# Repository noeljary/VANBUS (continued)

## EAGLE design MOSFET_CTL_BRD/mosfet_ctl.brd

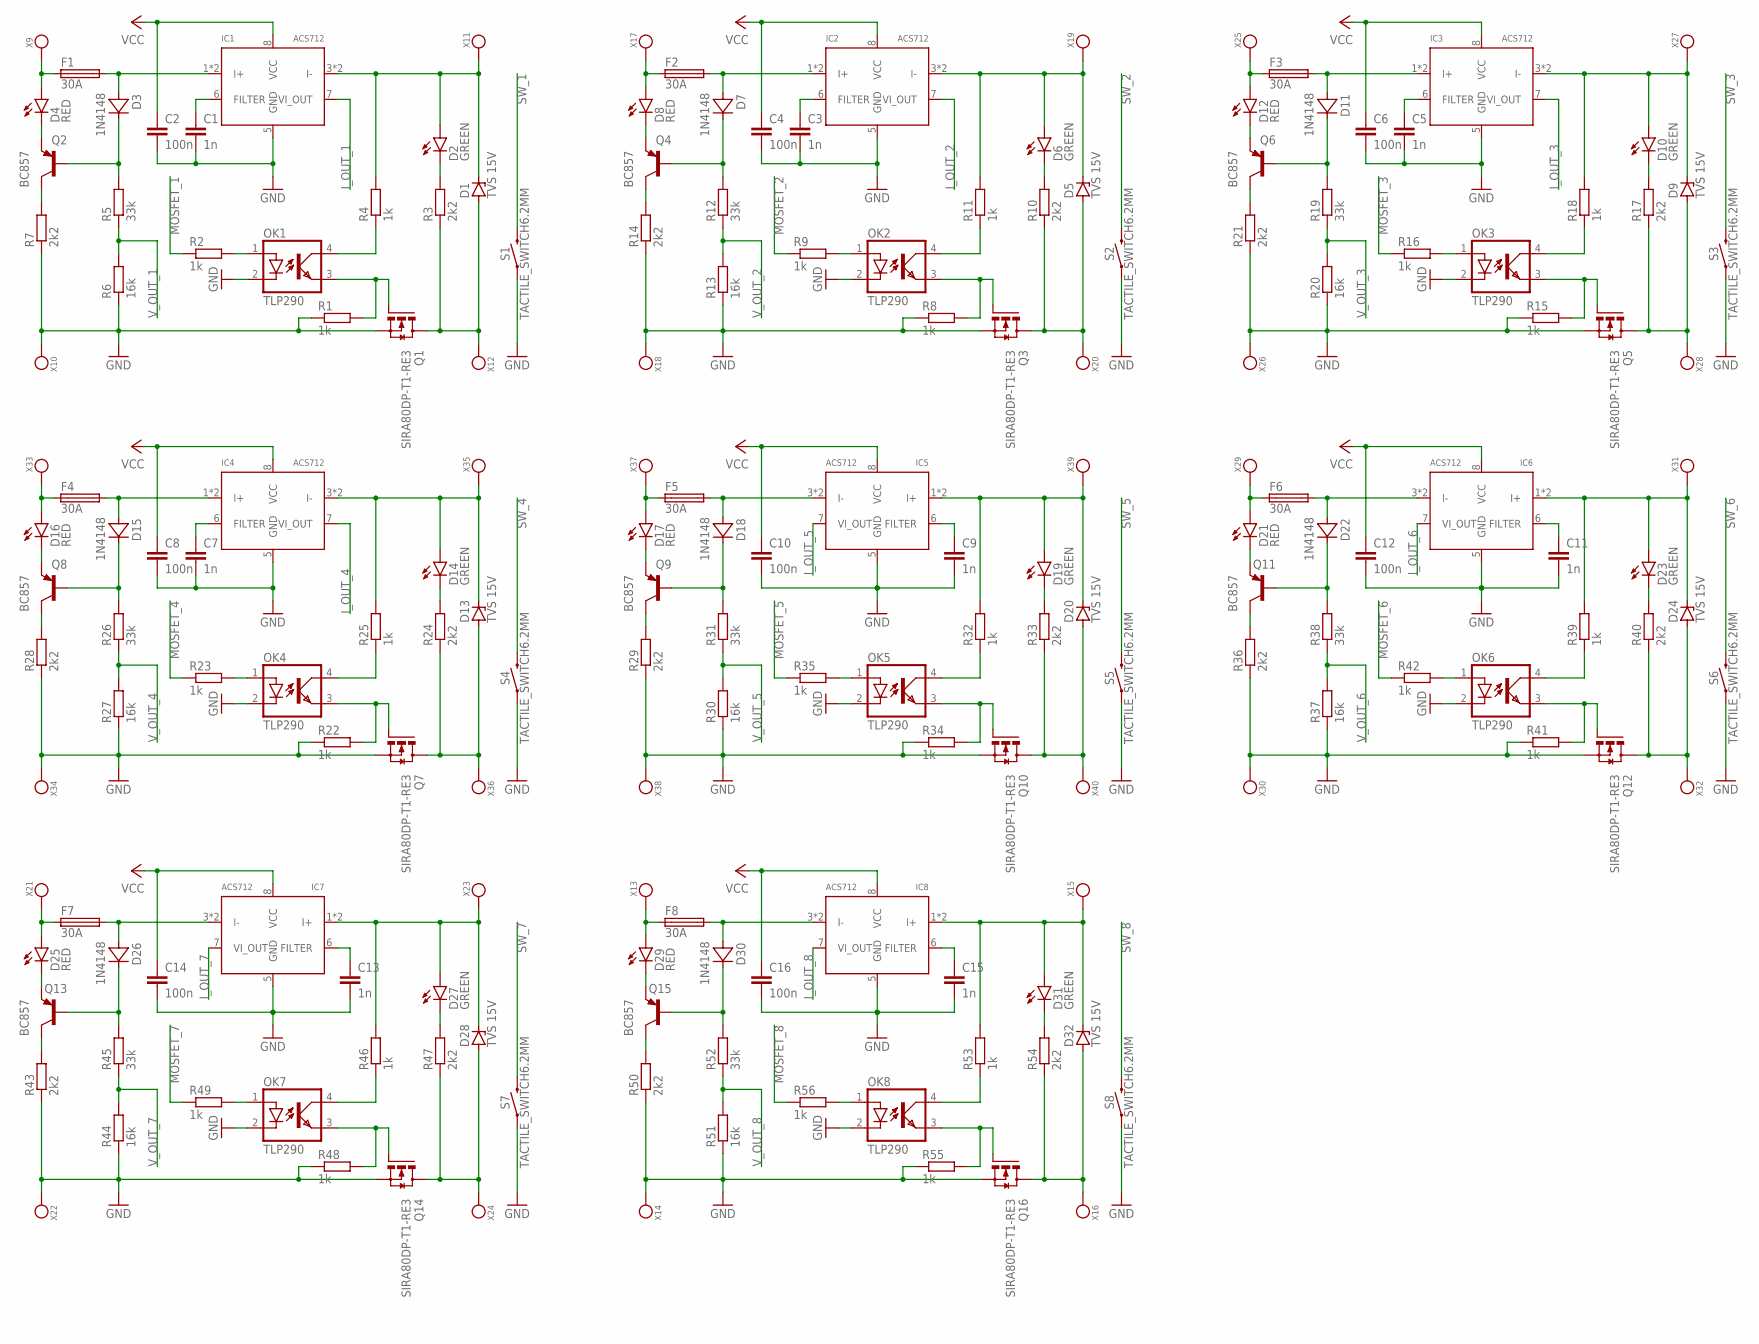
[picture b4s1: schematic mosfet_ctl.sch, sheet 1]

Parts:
C1, C3, C5, C7, C9, C11, C13, C15: 1n; C0805
C2, C4, C6, C8, C10, C12, C14, C16: 100n; C0805
D1, D5, D9, D13, D20, D24, D28, D32: TVS 15V; DO214AC
D2, D6, D10, D14, D19, D23, D27, D31: GREEN; CHIPLED_1206
D3, D7, D11, D15, D18, D22, D26, D30: 1N4148; SOD123
D4, D8, D12, D16, D17, D21, D25, D29: RED; CHIPLED_1206
F1, F2, F3, F4, F5, F6, F7, F8: 30A; KEYSTONE_3557-2
IC1, IC2, IC3, IC4, IC5, IC6, IC7, IC8: ACS712; SO08
OK1, OK2, OK3, OK4, OK5, OK6, OK7, OK8: TLP290; SO04
Q1, Q3, Q5, Q7, Q10, Q12, Q14, Q16: SIRA80DP-T1-RE3; POWERPAK-SO8
Q2, Q4, Q6, Q8, Q9, Q11, Q13, Q15: BC857; SOT23
R1, R2, R4, R8, R9, R11, R15, R16, R18, R22, R23, R25, R32, R34, R35, R39, R41, R42, R46, R48, R49, R53, R55, R56: 1k; R0805
R3, R7, R10, R14, R17, R21, R24, R28, R29, R33, R36, R40, R43, R47, R50, R54: 2k2; R0805
R5, R12, R19, R26, R31, R38, R45, R52: 33k; R0805
R6, R13, R20, R27, R30, R37, R44, R51: 16k; R0805
S1, S2, S3, S4, S5, S6, S7, S8: TACTILE_SWITCH6.2MM; TACTILE_SWITCH_SMD_6.2MM
X9, X10, X11, X12, X13, X14, X15, X16, X17, X18, X19, X20, X21, X22, X23, X24, X25, X26, X27, X28, X29, X30, X31, X32, X33, X34, X35, X36, X37, X38, X39, X40: KEYSTONE_7800

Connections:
GND: C1.2, C2.2, C3.2, C4.2, C5.2, C6.2, C7.2, C8.2, C9.2, C10.2, C11.2, C12.2, C13.2, C14.2, C15.2, C16.2, IC1.5 (GND), IC2.5 (GND), IC3.5 (GND), IC4.5 (GND), IC5.5 (GND), IC6.5 (GND), IC7.5 (GND), IC8.5 (GND), OK1.2 (C), OK2.2 (C), OK3.2 (C), OK4.2 (C), OK5.2 (C), OK6.2 (C), OK7.2 (C), OK8.2 (C), Q1.1 (S), Q1.2 (S), Q3.1 (S), Q3.2 (S), Q5.1 (S), Q5.2 (S), Q7.1 (S), Q7.2 (S), Q10.1 (S), Q10.2 (S), Q12.1 (S), Q12.2 (S), Q14.1 (S), Q14.2 (S), Q16.1 (S), Q16.2 (S), R1.1, R6.1, R7.1, R8.1, R13.1, R14.1, R15.1, R20.1, R21.1, R22.1, R27.1, R28.1, R29.1, R30.1, R34.1, R36.1, R37.1, R41.1, R43.1, R44.1, R48.1, R50.1, R51.1, R55.1, S1.A1 (1), S1.A2 (1), S2.A1 (1), S2.A2 (1), S3.A1 (1), S3.A2 (1), S4.A1 (1), S4.A2 (1), S5.A1 (1), S5.A2 (1), S6.A1 (1), S6.A2 (1), S7.A1 (1), S7.A2 (1), S8.A1 (1), S8.A2 (1), X10.1, X10.2, X10.3, X10.4, X10.5, X10.6, X14.1, X14.2, X14.3, X14.4, X14.5, X14.6, X18.1, X18.2, X18.3, X18.4, X18.5, X18.6, X22.1, X22.2, X22.3, X22.4, X22.5, X22.6, X26.1, X26.2, X26.3, X26.4, X26.5, X26.6, X30.1, X30.2, X30.3, X30.4, X30.5, X30.6, X34.1, X34.2, X34.3, X34.4, X34.5, X34.6, X38.1, X38.2, X38.3, X38.4, X38.5, X38.6; also elsewhere on the board
I_OUT_1: IC1.7 (VI_OUT); also elsewhere on the board
I_OUT_2: IC2.7 (VI_OUT); also elsewhere on the board
I_OUT_3: IC3.7 (VI_OUT); also elsewhere on the board
I_OUT_4: IC4.7 (VI_OUT); also elsewhere on the board
I_OUT_5: IC5.7 (VI_OUT); also elsewhere on the board
I_OUT_6: IC6.7 (VI_OUT); also elsewhere on the board
I_OUT_7: IC7.7 (VI_OUT); also elsewhere on the board
I_OUT_8: IC8.7 (VI_OUT); also elsewhere on the board
MOSFET_1: R2.1; also elsewhere on the board
MOSFET_2: R9.1; also elsewhere on the board
MOSFET_3: R16.1; also elsewhere on the board
MOSFET_4: R23.1; also elsewhere on the board
MOSFET_5: R35.1; also elsewhere on the board
MOSFET_6: R42.1; also elsewhere on the board
MOSFET_7: R49.1; also elsewhere on the board
MOSFET_8: R56.1; also elsewhere on the board
unnamed: D4.A, F1.1, F1.3 (1), X9.1, X9.2, X9.3, X9.4, X9.5, X9.6
unnamed: D3.A, F1.2, F1.4 (2), IC1.1 (I+), IC1.2 (I+)
unnamed: D4.C, Q2.2 (E)
unnamed: D3.C, Q2.3 (B), R5.2
unnamed: Q2.1 (C), R7.2
unnamed: C1.1, IC1.6 (FILTER)
unnamed: D2.C, R3.2
unnamed: OK1.1 (A), R2.2
unnamed: OK1.4 (COL), R4.1
unnamed: D1.C, D2.A, IC1.3 (I-), IC1.4 (I-), R4.2, X11.1, X11.2, X11.3, X11.4, X11.5, X11.6
unnamed: OK1.3 (EMIT), Q1.3 (G), Q1.4 (G), R1.2
unnamed: D1.A, Q1.5 (D), Q1.6 (D), Q1.7 (D), Q1.8 (D), Q1.9 (D), R3.1, X12.1, X12.2, X12.3, X12.4, X12.5, X12.6
unnamed: D29.A, F8.1, F8.3 (1), X13.1, X13.2, X13.3, X13.4, X13.5, X13.6
unnamed: D30.A, F8.2, F8.4 (2), IC8.3 (I-), IC8.4 (I-)
unnamed: D29.C, Q15.2 (E)
unnamed: D30.C, Q15.3 (B), R52.2
unnamed: Q15.1 (C), R50.2
unnamed: C15.1, IC8.6 (FILTER)
unnamed: D31.C, R54.2
unnamed: OK8.1 (A), R56.2
unnamed: OK8.4 (COL), R53.1
unnamed: D31.A, D32.C, IC8.1 (I+), IC8.2 (I+), R53.2, X15.1, X15.2, X15.3, X15.4, X15.5, X15.6
unnamed: OK8.3 (EMIT), Q16.3 (G), Q16.4 (G), R55.2
unnamed: D32.A, Q16.5 (D), Q16.6 (D), Q16.7 (D), Q16.8 (D), Q16.9 (D), R54.1, X16.1, X16.2, X16.3, X16.4, X16.5, X16.6
unnamed: D8.A, F2.1, F2.3 (1), X17.1, X17.2, X17.3, X17.4, X17.5, X17.6
unnamed: D7.A, F2.2, F2.4 (2), IC2.1 (I+), IC2.2 (I+)
unnamed: D8.C, Q4.2 (E)
unnamed: D7.C, Q4.3 (B), R12.2
unnamed: Q4.1 (C), R14.2
unnamed: C3.1, IC2.6 (FILTER)
unnamed: D6.C, R10.2
unnamed: OK2.1 (A), R9.2
unnamed: OK2.4 (COL), R11.1
unnamed: D5.C, D6.A, IC2.3 (I-), IC2.4 (I-), R11.2, X19.1, X19.2, X19.3, X19.4, X19.5, X19.6
unnamed: OK2.3 (EMIT), Q3.3 (G), Q3.4 (G), R8.2
unnamed: D5.A, Q3.5 (D), Q3.6 (D), Q3.7 (D), Q3.8 (D), Q3.9 (D), R10.1, X20.1, X20.2, X20.3, X20.4, X20.5, X20.6
unnamed: D25.A, F7.1, F7.3 (1), X21.1, X21.2, X21.3, X21.4, X21.5, X21.6
unnamed: D26.A, F7.2, F7.4 (2), IC7.3 (I-), IC7.4 (I-)
unnamed: D25.C, Q13.2 (E)
unnamed: D26.C, Q13.3 (B), R45.2
unnamed: Q13.1 (C), R43.2
unnamed: C13.1, IC7.6 (FILTER)
unnamed: D27.C, R47.2
unnamed: OK7.1 (A), R49.2
unnamed: OK7.4 (COL), R46.1
unnamed: D27.A, D28.C, IC7.1 (I+), IC7.2 (I+), R46.2, X23.1, X23.2, X23.3, X23.4, X23.5, X23.6
unnamed: OK7.3 (EMIT), Q14.3 (G), Q14.4 (G), R48.2
unnamed: D28.A, Q14.5 (D), Q14.6 (D), Q14.7 (D), Q14.8 (D), Q14.9 (D), R47.1, X24.1, X24.2, X24.3, X24.4, X24.5, X24.6
unnamed: D12.A, F3.1, F3.3 (1), X25.1, X25.2, X25.3, X25.4, X25.5, X25.6
unnamed: D11.A, F3.2, F3.4 (2), IC3.1 (I+), IC3.2 (I+)
unnamed: D12.C, Q6.2 (E)
unnamed: D11.C, Q6.3 (B), R19.2
unnamed: Q6.1 (C), R21.2
unnamed: C5.1, IC3.6 (FILTER)
unnamed: D10.C, R17.2
unnamed: OK3.1 (A), R16.2
unnamed: OK3.4 (COL), R18.1
unnamed: D9.C, D10.A, IC3.3 (I-), IC3.4 (I-), R18.2, X27.1, X27.2, X27.3, X27.4, X27.5, X27.6
unnamed: OK3.3 (EMIT), Q5.3 (G), Q5.4 (G), R15.2
unnamed: D9.A, Q5.5 (D), Q5.6 (D), Q5.7 (D), Q5.8 (D), Q5.9 (D), R17.1, X28.1, X28.2, X28.3, X28.4, X28.5, X28.6
unnamed: D21.A, F6.1, F6.3 (1), X29.1, X29.2, X29.3, X29.4, X29.5, X29.6
unnamed: D22.A, F6.2, F6.4 (2), IC6.3 (I-), IC6.4 (I-)
unnamed: D21.C, Q11.2 (E)
unnamed: D22.C, Q11.3 (B), R38.2
unnamed: Q11.1 (C), R36.2
unnamed: C11.1, IC6.6 (FILTER)
unnamed: D23.C, R40.2
unnamed: OK6.1 (A), R42.2
unnamed: OK6.4 (COL), R39.1
unnamed: D23.A, D24.C, IC6.1 (I+), IC6.2 (I+), R39.2, X31.1, X31.2, X31.3, X31.4, X31.5, X31.6
unnamed: OK6.3 (EMIT), Q12.3 (G), Q12.4 (G), R41.2
unnamed: D24.A, Q12.5 (D), Q12.6 (D), Q12.7 (D), Q12.8 (D), Q12.9 (D), R40.1, X32.1, X32.2, X32.3, X32.4, X32.5, X32.6
unnamed: D16.A, F4.1, F4.3 (1), X33.1, X33.2, X33.3, X33.4, X33.5, X33.6
unnamed: D15.A, F4.2, F4.4 (2), IC4.1 (I+), IC4.2 (I+)
unnamed: D16.C, Q8.2 (E)
unnamed: D15.C, Q8.3 (B), R26.2
unnamed: Q8.1 (C), R28.2
unnamed: C7.1, IC4.6 (FILTER)
unnamed: D14.C, R24.2
unnamed: OK4.1 (A), R23.2
unnamed: OK4.4 (COL), R25.1
unnamed: D13.C, D14.A, IC4.3 (I-), IC4.4 (I-), R25.2, X35.1, X35.2, X35.3, X35.4, X35.5, X35.6
unnamed: OK4.3 (EMIT), Q7.3 (G), Q7.4 (G), R22.2
unnamed: D13.A, Q7.5 (D), Q7.6 (D), Q7.7 (D), Q7.8 (D), Q7.9 (D), R24.1, X36.1, X36.2, X36.3, X36.4, X36.5, X36.6
unnamed: D17.A, F5.1, F5.3 (1), X37.1, X37.2, X37.3, X37.4, X37.5, X37.6
unnamed: D18.A, F5.2, F5.4 (2), IC5.3 (I-), IC5.4 (I-)
unnamed: D17.C, Q9.2 (E)
unnamed: D18.C, Q9.3 (B), R31.2
unnamed: Q9.1 (C), R29.2
unnamed: C9.1, IC5.6 (FILTER)
unnamed: D19.C, R33.2
unnamed: OK5.1 (A), R35.2
unnamed: OK5.4 (COL), R32.1
unnamed: D19.A, D20.C, IC5.1 (I+), IC5.2 (I+), R32.2, X39.1, X39.2, X39.3, X39.4, X39.5, X39.6
unnamed: OK5.3 (EMIT), Q10.3 (G), Q10.4 (G), R34.2
unnamed: D20.A, Q10.5 (D), Q10.6 (D), Q10.7 (D), Q10.8 (D), Q10.9 (D), R33.1, X40.1, X40.2, X40.3, X40.4, X40.5, X40.6
SW_1: S1.B1 (2), S1.B2 (2); also elsewhere on the board
SW_2: S2.B1 (2), S2.B2 (2); also elsewhere on the board
SW_3: S3.B1 (2), S3.B2 (2); also elsewhere on the board
SW_4: S4.B1 (2), S4.B2 (2); also elsewhere on the board
SW_5: S5.B1 (2), S5.B2 (2); also elsewhere on the board
SW_6: S6.B1 (2), S6.B2 (2); also elsewhere on the board
SW_7: S7.B1 (2), S7.B2 (2); also elsewhere on the board
SW_8: S8.B1 (2), S8.B2 (2); also elsewhere on the board
VCC: C2.1, C4.1, C6.1, C8.1, C10.1, C12.1, C14.1, C16.1, IC1.8 (VCC), IC2.8 (VCC), IC3.8 (VCC), IC4.8 (VCC), IC5.8 (VCC), IC6.8 (VCC), IC7.8 (VCC), IC8.8 (VCC); also elsewhere on the board
V_OUT_1: R5.1, R6.2; also elsewhere on the board
V_OUT_2: R12.1, R13.2; also elsewhere on the board
V_OUT_3: R19.1, R20.2; also elsewhere on the board
V_OUT_4: R26.1, R27.2; also elsewhere on the board
V_OUT_5: R30.2, R31.1; also elsewhere on the board
V_OUT_6: R37.2, R38.1; also elsewhere on the board
V_OUT_7: R44.2, R45.1; also elsewhere on the board
V_OUT_8: R51.2, R52.1; also elsewhere on the board

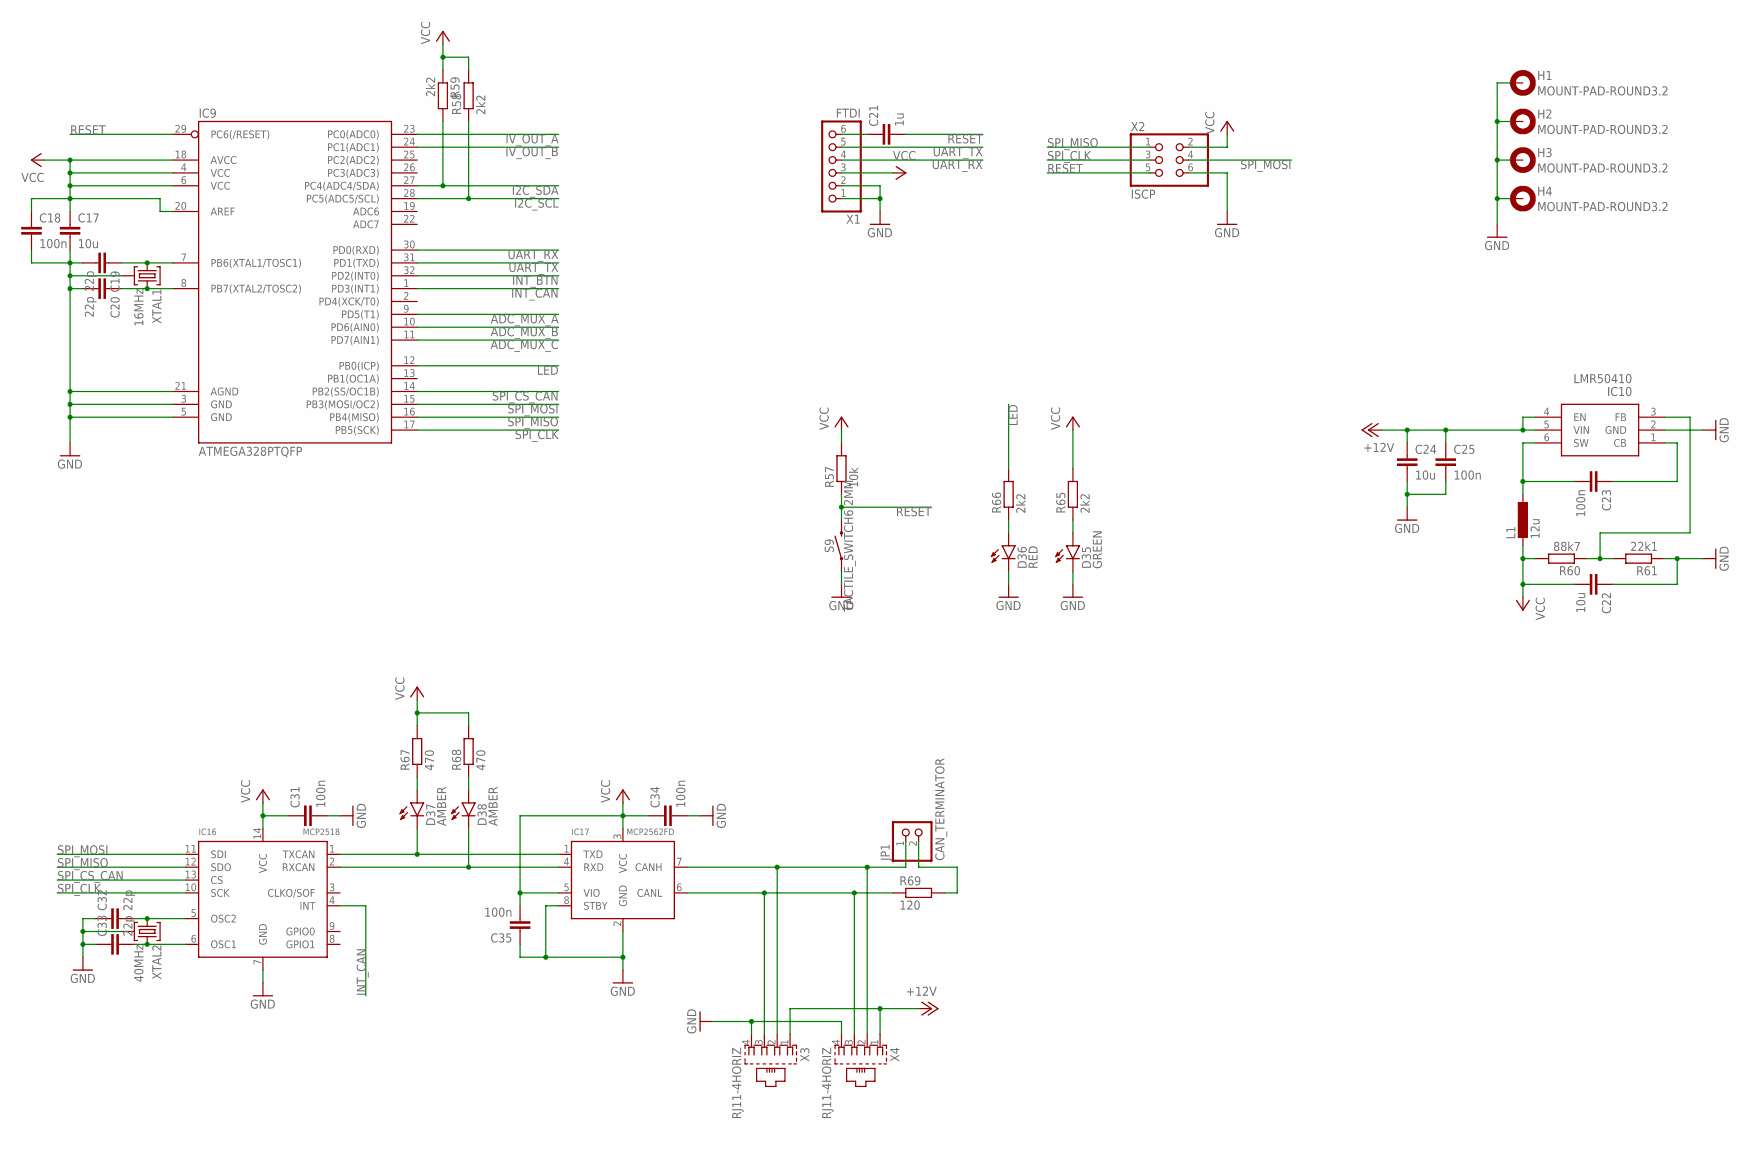
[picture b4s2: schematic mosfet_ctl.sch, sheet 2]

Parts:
C17, C22, C24: 10u; C1206
C18, C23, C25, C31, C34, C35: 100n; C0805
C19, C20, C32, C33: 22p; C0805
C21: 1u; C0805
D35: GREEN; CHIPLED_1206
D36: RED; CHIPLED_1206
D37, D38: AMBER; CHIPLED_1206
H1, H2, H3, H4: MOUNT-PAD-ROUND3.2; 3,2-PAD
IC9: ATMEGA328PTQFP; TQFP32_0.8MM_7X7MM
IC10: LMR50410; SOT23-6
IC16: MCP2518; SO14
IC17: MCP2562FD; SO08
JP1: CAN_TERMINATOR; 1X02
L1: 12u; L_7.3MM
R57: 10k; R0805
R58, R59, R65, R66: 2k2; R0805
R60: 88k7; R0805
R61: 22k1; R0805
R67, R68: 470; R0805
R69: 120; R0805
S9: TACTILE_SWITCH6.2MM; TACTILE_SWITCH_SMD_6.2MM
X1: FTDI; 1X06
X2: ISCP; 2X03
X3, X4: RJ11-4HORIZ; RJ11-4_HORIZ
XTAL1: 16MHz; XTAL_5.0X3.2_4
XTAL2: 40MHz; XTAL_5.0X3.2_4

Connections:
+12V: C24.1, C25.1, IC10.4 (EN), IC10.5 (VIN), X3.1, X4.1
ADC_MUX_A: IC9.9 (PD5(T1)); also elsewhere on the board
ADC_MUX_B: IC9.10 (PD6(AIN0)); also elsewhere on the board
ADC_MUX_C: IC9.11 (PD7(AIN1)); also elsewhere on the board
GND: C17.2, C18.2, C19.2, C20.2, C22.1, C24.2, C25.2, C31.2, C32.1, C33.1, C34.2, C35.1, D35.C, D36.C, H1.B3,2, H1.P$1, H1.P$2, H1.P$3, H1.P$4, H1.P$5, H1.P$6, H1.P$7, H1.P$8, H2.B3,2, H2.P$1, H2.P$2, H2.P$3, H2.P$4, H2.P$5, H2.P$6, H2.P$7, H2.P$8, H3.B3,2, H3.P$1, H3.P$2, H3.P$3, H3.P$4, H3.P$5, H3.P$6, H3.P$7, H3.P$8, H4.B3,2, H4.P$1, H4.P$2, H4.P$3, H4.P$4, H4.P$5, H4.P$6, H4.P$7, H4.P$8, IC9.3 (GND), IC9.5 (GND), IC9.21 (AGND), IC10.2 (GND), IC16.7 (GND), IC17.2 (GND), IC17.8 (STBY), R61.1, S9.A1 (1), S9.A2 (1), X1.1, X1.2, X2.6, X3.4, X4.4, XTAL1.2, XTAL1.4 (2), XTAL2.2, XTAL2.4 (2); also elsewhere on the board
I2C_SCL: IC9.28 (PC5(ADC5/SCL)), R58.1; also elsewhere on the board
I2C_SDA: IC9.27 (PC4(ADC4/SDA)), R59.2; also elsewhere on the board
INT_BTN: IC9.32 (PD2(INT0)); also elsewhere on the board
INT_CAN: IC9.1 (PD3(INT1)), IC16.4 (INT)
IV_OUT_A: IC9.23 (PC0(ADC0)); also elsewhere on the board
IV_OUT_B: IC9.24 (PC1(ADC1)); also elsewhere on the board
LED: IC9.12 (PB0(ICP)), R66.2
unnamed: D36.A, R66.1
unnamed: C19.1, IC9.7 (PB6(XTAL1/TOSC1)), XTAL1.1
unnamed: C20.1, IC9.8 (PB7(XTAL2/TOSC2)), XTAL1.3
unnamed: D35.A, R65.1
unnamed: C21.1, X1.6
unnamed: IC17.6 (CANL), R69.1, X3.3, X4.3
unnamed: IC17.7 (CANH), JP1.1, X3.2, X4.2
unnamed: D37.C, IC16.1 (TXCAN), IC17.1 (TXD)
unnamed: D38.C, IC16.2 (RXCAN), IC17.4 (RXD)
unnamed: C32.2, IC16.5 (OSC2), XTAL2.1
unnamed: C33.2, IC16.6 (OSC1), XTAL2.3
unnamed: D37.A, R67.1
unnamed: D38.A, R68.1
unnamed: JP1.2, R69.2
unnamed: C23.2, IC10.6 (SW), L1.1
unnamed: C23.1, IC10.1 (CB)
unnamed: IC10.3 (FB), R60.1, R61.2
RESET: C21.2, IC9.29 (PC6(/RESET)), R57.1, S9.B1 (2), S9.B2 (2), X2.5; also elsewhere on the board
SPI_CLK: IC9.17 (PB5(SCK)), IC16.10 (SCK), X2.3
SPI_CS_CAN: IC9.14 (PB2(SS/OC1B)), IC16.13 (CS)
SPI_MISO: IC9.16 (PB4(MISO)), IC16.12 (SDO), X2.1
SPI_MOSI: IC9.15 (PB3(MOSI/OC2)), IC16.11 (SDI), X2.4
UART_RX: IC9.30 (PD0(RXD)), X1.4
UART_TX: IC9.31 (PD1(TXD)), X1.5
VCC: C17.1, C18.1, C22.2, C31.1, C34.1, C35.2, IC9.4 (VCC), IC9.6 (VCC), IC9.18 (AVCC), IC9.20 (AREF), IC16.14 (VCC), IC17.3 (VCC), IC17.5 (VIO), L1.2, R57.2, R58.2, R59.1, R60.2, R65.2, R67.2, R68.2, X1.3, X2.2; also elsewhere on the board

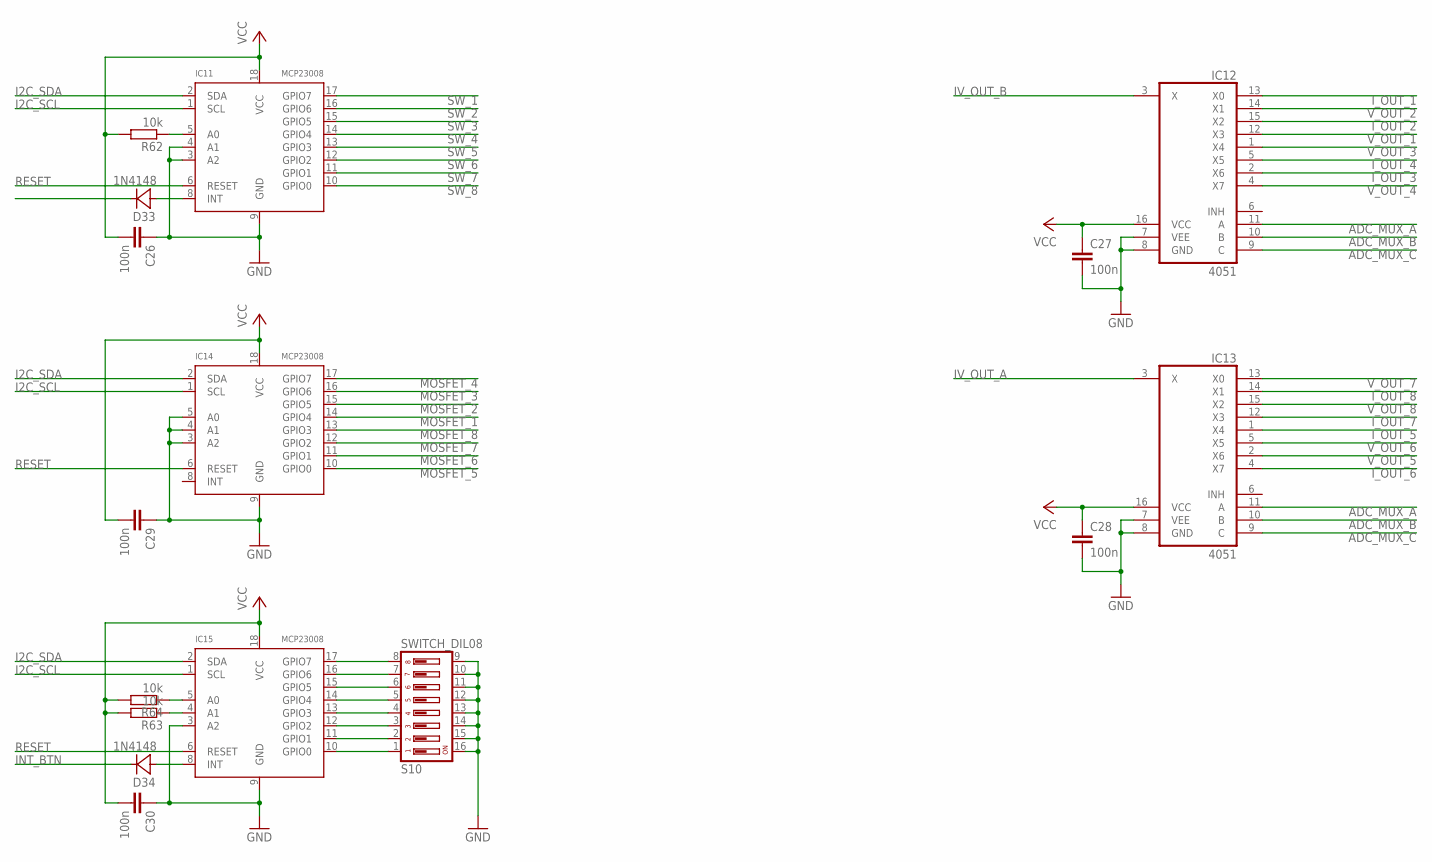
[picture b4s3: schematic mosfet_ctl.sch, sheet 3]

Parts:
C26, C27, C28, C29, C30: 100n; C0805
D33, D34: 1N4148; SOD123
IC11, IC14, IC15: MCP23008; SO18W
IC12, IC13: 4051; SO16
R62, R63, R64: 10k; R0805
S10: SWITCH_DIL08; CTS-219-08

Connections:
ADC_MUX_A: IC12.11 (A), IC13.11 (A); also elsewhere on the board
ADC_MUX_B: IC12.10 (B), IC13.10 (B); also elsewhere on the board
ADC_MUX_C: IC12.9 (C), IC13.9 (C); also elsewhere on the board
GND: C26.1, C27.2, C28.2, C29.1, C30.1, IC11.3 (A2), IC11.4 (A1), IC11.9 (GND), IC12.7 (VEE), IC12.8 (GND), IC13.7 (VEE), IC13.8 (GND), IC14.3 (A2), IC14.4 (A1), IC14.5 (A0), IC14.9 (GND), IC15.3 (A2), IC15.9 (GND), S10.9, S10.10, S10.11, S10.12, S10.13, S10.14, S10.15, S10.16; also elsewhere on the board
I2C_SCL: IC11.1 (SCL), IC14.1 (SCL), IC15.1 (SCL); also elsewhere on the board
I2C_SDA: IC11.2 (SDA), IC14.2 (SDA), IC15.2 (SDA); also elsewhere on the board
INT_BTN: D33.C, D34.C; also elsewhere on the board
IV_OUT_A: IC13.3 (X); also elsewhere on the board
IV_OUT_B: IC12.3 (X); also elsewhere on the board
I_OUT_1: IC12.13 (X0); also elsewhere on the board
I_OUT_2: IC12.15 (X2); also elsewhere on the board
I_OUT_3: IC12.2 (X6); also elsewhere on the board
I_OUT_4: IC12.5 (X5); also elsewhere on the board
I_OUT_5: IC13.1 (X4); also elsewhere on the board
I_OUT_6: IC13.4 (X7); also elsewhere on the board
I_OUT_7: IC13.12 (X3); also elsewhere on the board
I_OUT_8: IC13.14 (X1); also elsewhere on the board
MOSFET_1: IC14.14 (GPIO4); also elsewhere on the board
MOSFET_2: IC14.15 (GPIO5); also elsewhere on the board
MOSFET_3: IC14.16 (GPIO6); also elsewhere on the board
MOSFET_4: IC14.17 (GPIO7); also elsewhere on the board
MOSFET_5: IC14.10 (GPIO0); also elsewhere on the board
MOSFET_6: IC14.11 (GPIO1); also elsewhere on the board
MOSFET_7: IC14.12 (GPIO2); also elsewhere on the board
MOSFET_8: IC14.13 (GPIO3); also elsewhere on the board
unnamed: IC11.5 (A0), R62.1
unnamed: IC15.5 (A0), R64.1
unnamed: IC15.4 (A1), R63.1
unnamed: IC15.10 (GPIO0), S10.1
unnamed: IC15.11 (GPIO1), S10.2
unnamed: IC15.12 (GPIO2), S10.3
unnamed: IC15.13 (GPIO3), S10.4
unnamed: IC15.14 (GPIO4), S10.5
unnamed: IC15.15 (GPIO5), S10.6
unnamed: IC15.16 (GPIO6), S10.7
unnamed: IC15.17 (GPIO7), S10.8
unnamed: D33.A, IC11.8 (INT)
unnamed: D34.A, IC15.8 (INT)
RESET: IC11.6 (RESET), IC14.6 (RESET), IC15.6 (RESET); also elsewhere on the board
SW_1: IC11.17 (GPIO7); also elsewhere on the board
SW_2: IC11.16 (GPIO6); also elsewhere on the board
SW_3: IC11.15 (GPIO5); also elsewhere on the board
SW_4: IC11.14 (GPIO4); also elsewhere on the board
SW_5: IC11.13 (GPIO3); also elsewhere on the board
SW_6: IC11.12 (GPIO2); also elsewhere on the board
SW_7: IC11.11 (GPIO1); also elsewhere on the board
SW_8: IC11.10 (GPIO0); also elsewhere on the board
VCC: C26.2, C27.1, C28.1, C29.2, C30.2, IC11.18 (VCC), IC12.16 (VCC), IC13.16 (VCC), IC14.18 (VCC), IC15.18 (VCC), R62.2, R63.2, R64.2; also elsewhere on the board
V_OUT_1: IC12.12 (X3); also elsewhere on the board
V_OUT_2: IC12.14 (X1); also elsewhere on the board
V_OUT_3: IC12.1 (X4); also elsewhere on the board
V_OUT_4: IC12.4 (X7); also elsewhere on the board
V_OUT_5: IC13.2 (X6); also elsewhere on the board
V_OUT_6: IC13.5 (X5); also elsewhere on the board
V_OUT_7: IC13.13 (X0); also elsewhere on the board
V_OUT_8: IC13.15 (X2); also elsewhere on the board

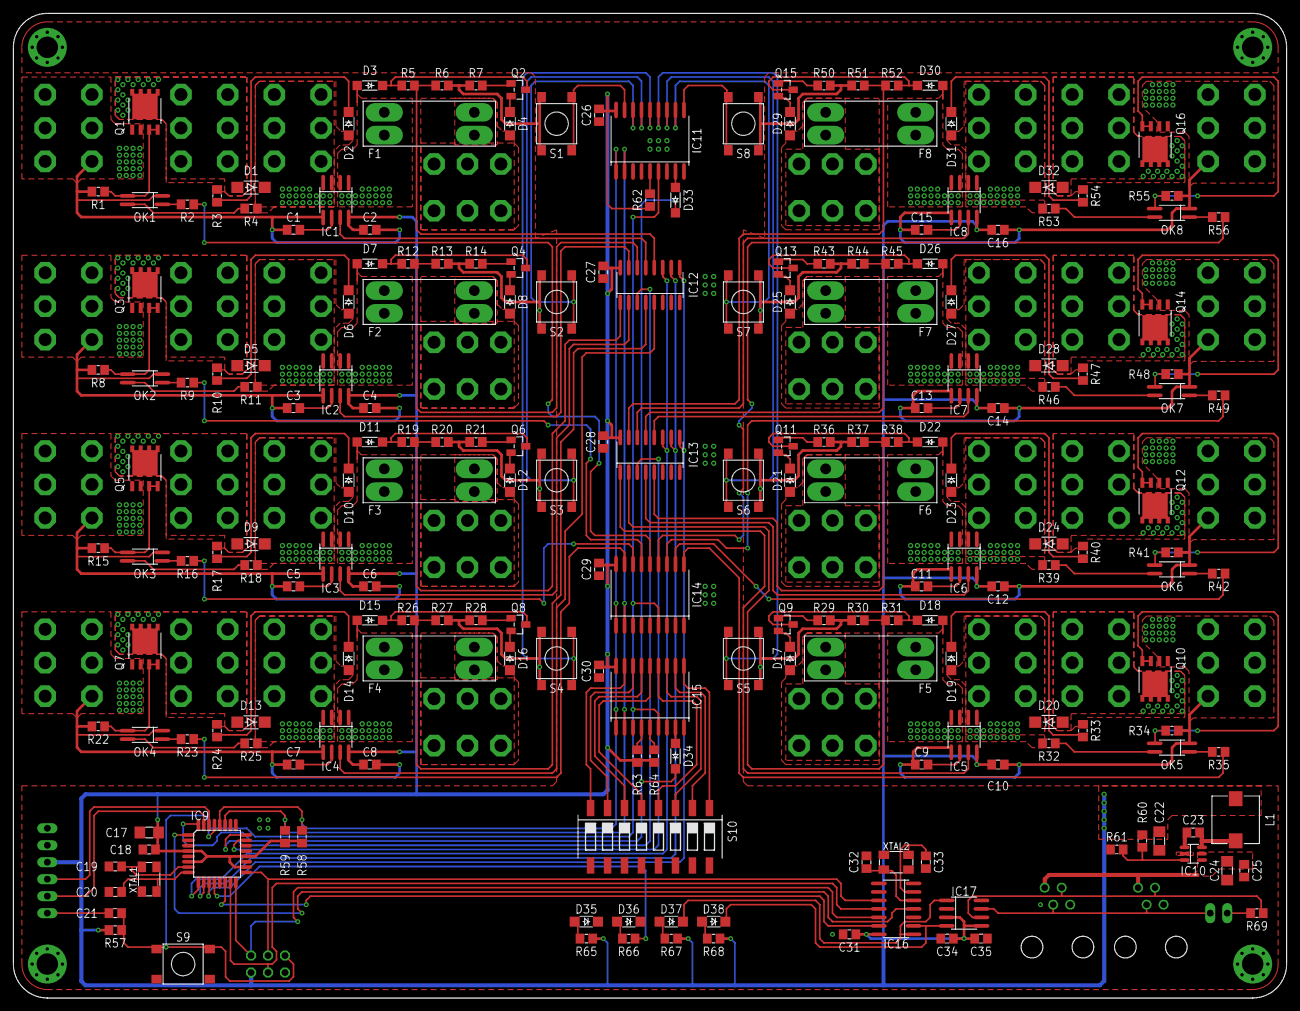
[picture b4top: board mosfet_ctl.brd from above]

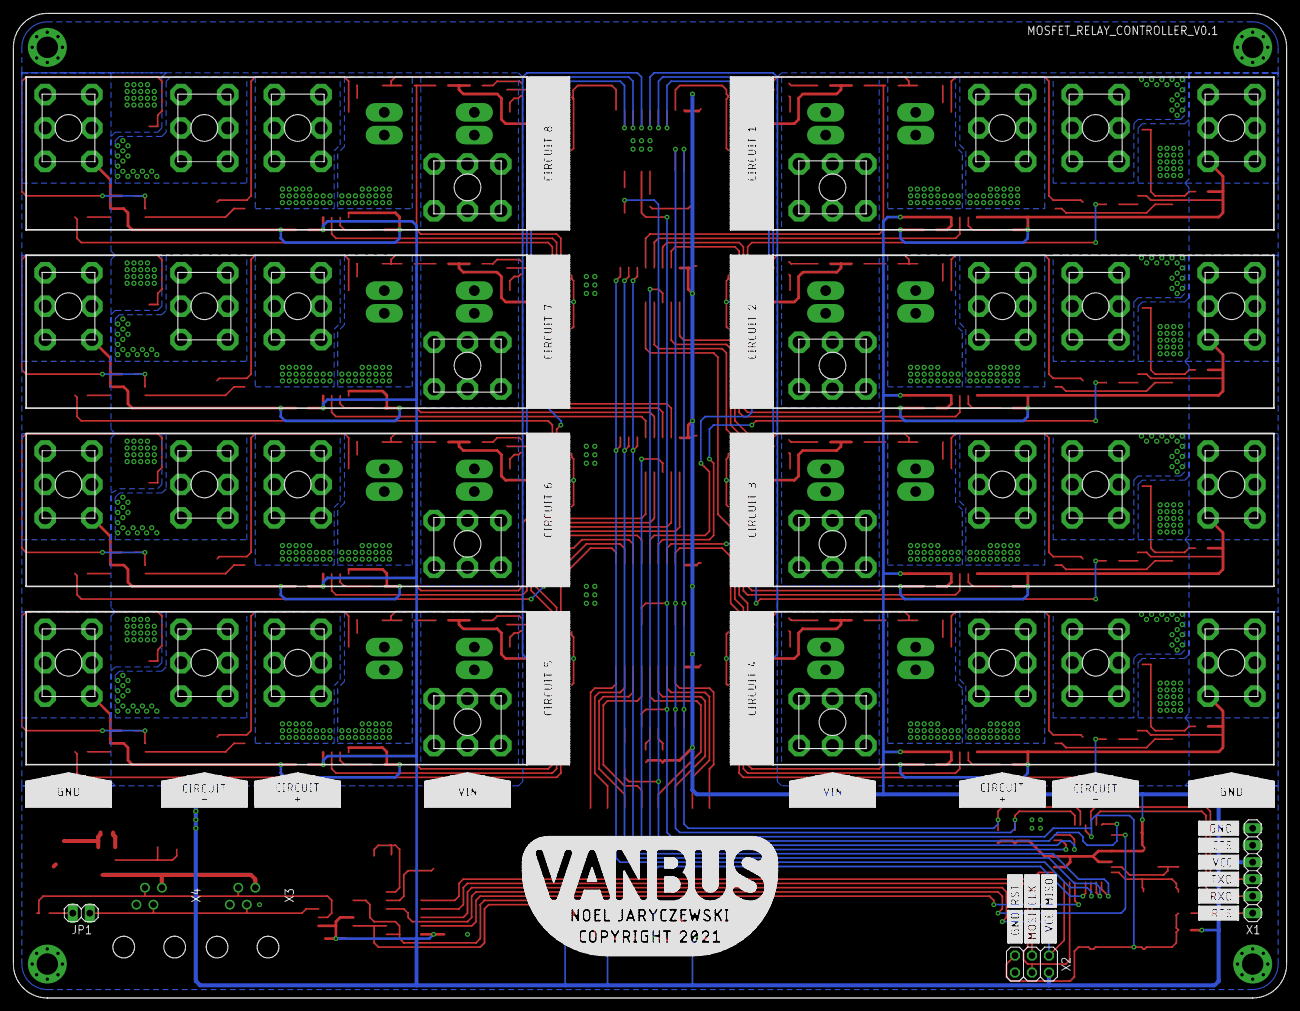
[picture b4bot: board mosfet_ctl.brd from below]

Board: 2 copper layers, 190.5 x 147.3 mm, 245 parts (37 on the bottom side), 178 nets.

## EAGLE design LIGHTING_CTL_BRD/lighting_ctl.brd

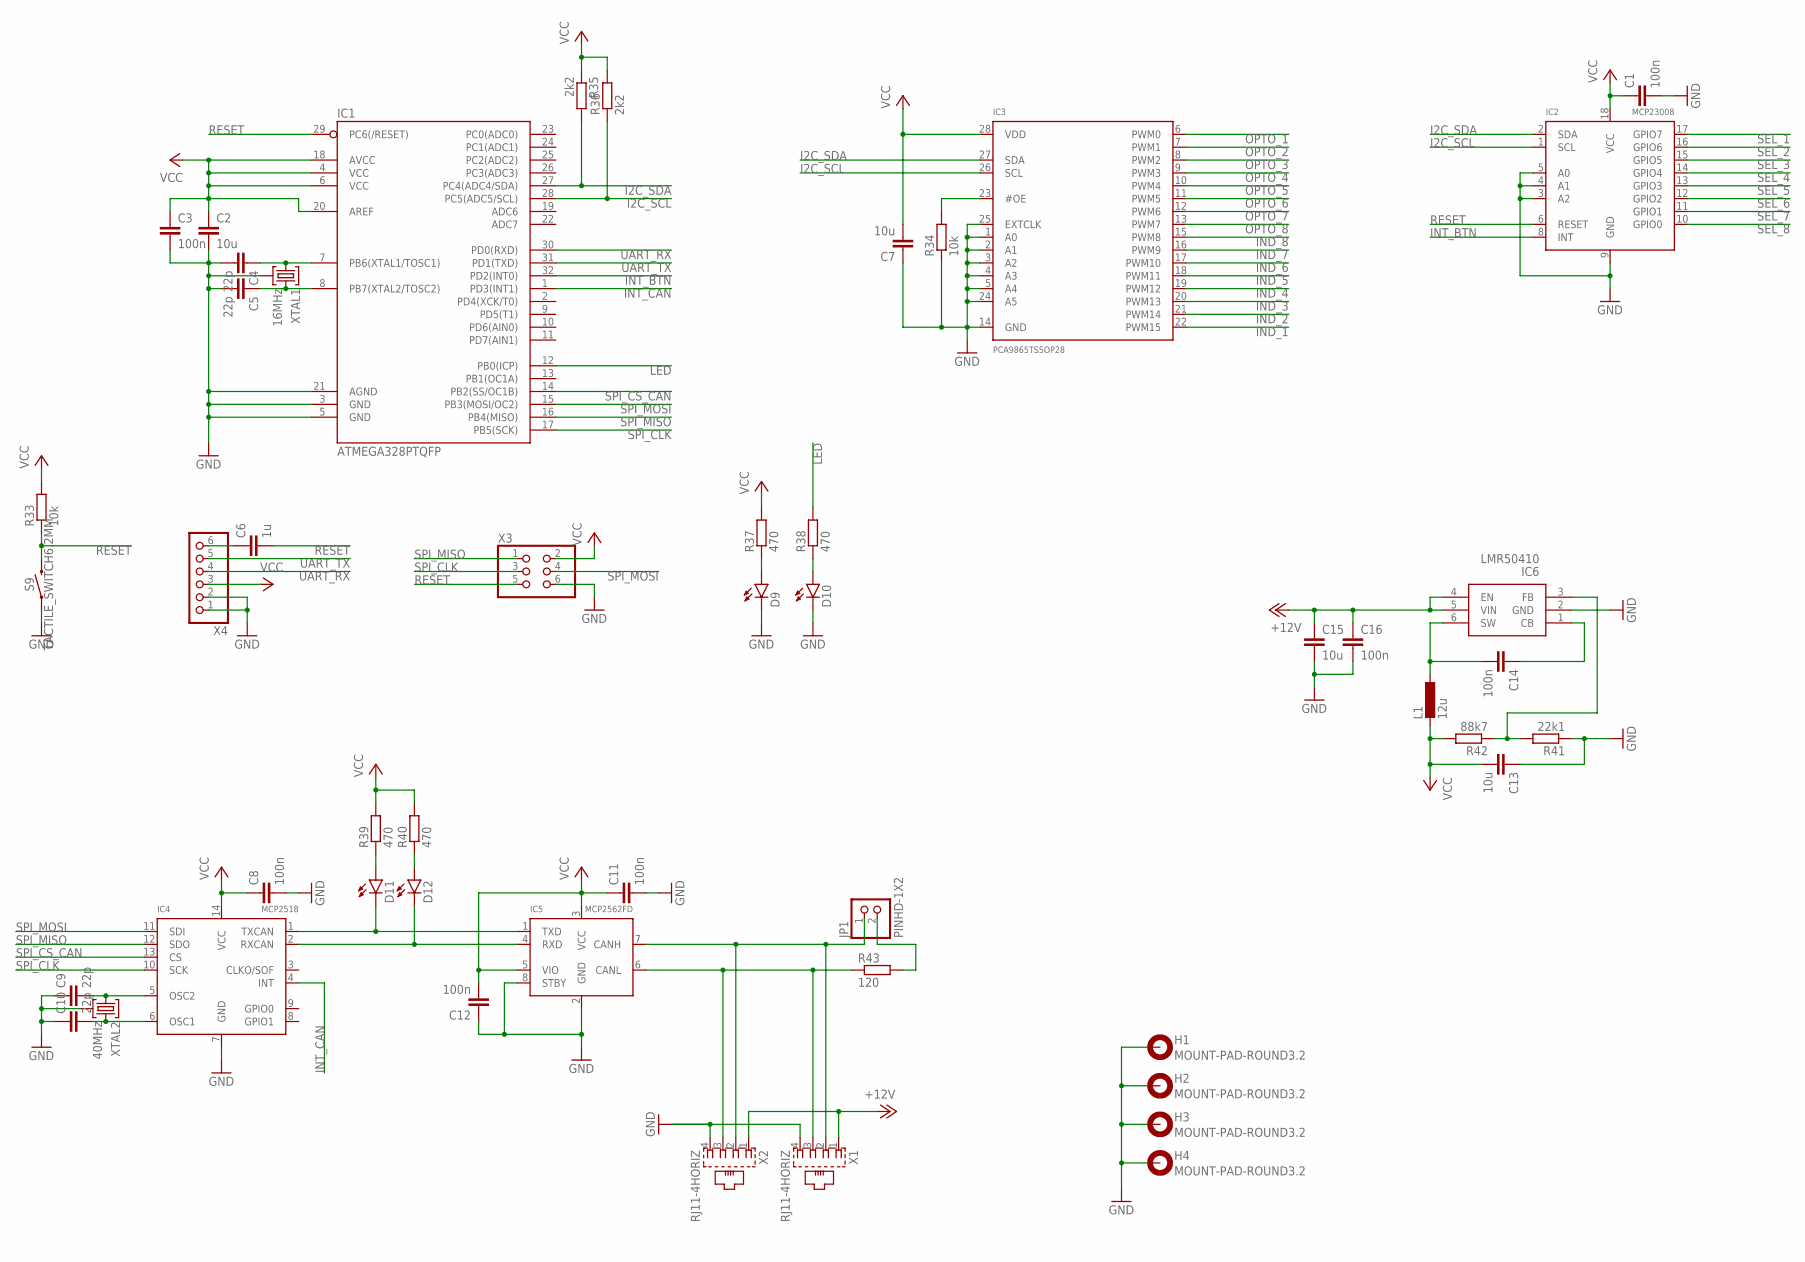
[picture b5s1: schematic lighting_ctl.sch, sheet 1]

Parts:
C1, C3, C8, C11, C12, C14, C16: 100n; C0805
C2, C7, C13, C15: 10u; C1206
C4, C5, C9, C10: 22p; C0805
C6: 1u; C0805
D9, D10, D11, D12: LED1206; CHIPLED_1206
H1, H2, H3, H4: MOUNT-PAD-ROUND3.2; 3,2-PAD
IC1: ATMEGA328PTQFP; TQFP32_0.8MM_7X7MM
IC2: MCP23008; SO18W
IC3: PCA9865TSSOP28; TSSOP28
IC4: MCP2518; SO14
IC5: MCP2562FD; SO08
IC6: LMR50410; SOT23-6
JP1: PINHD-1X2; 1X02
L1: 12u; L_7.3MM
R33, R34: 10k; R0805
R35, R36: 2k2; R0805
R37, R38, R39, R40: 470; R0805
R41: 22k1; R0805
R42: 88k7; R0805
R43: 120; R0805
S9: TACTILE_SWITCH6.2MM; TACTILE_SWITCH_SMD_6.2MM
X1, X2: RJ11-4HORIZ; RJ11-4_HORIZ
X3: PINHD-2X3; 2X03
X4: PINHD-1X6; 1X06
XTAL1: 16MHz; XTAL_5.0X3.2_4
XTAL2: 40MHz; XTAL_5.0X3.2_4

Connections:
+12V: C15.1, C16.1, IC6.4 (EN), IC6.5 (VIN), X1.1, X2.1
GND: C1.2, C2.2, C3.2, C4.2, C5.2, C7.1, C8.2, C9.1, C10.1, C11.2, C12.1, C13.1, C15.2, C16.2, D9.C, D10.C, H1.B3,2, H1.P$1, H1.P$2, H1.P$3, H1.P$4, H1.P$5, H1.P$6, H1.P$7, H1.P$8, H2.B3,2, H2.P$1, H2.P$2, H2.P$3, H2.P$4, H2.P$5, H2.P$6, H2.P$7, H2.P$8, H3.B3,2, H3.P$1, H3.P$2, H3.P$3, H3.P$4, H3.P$5, H3.P$6, H3.P$7, H3.P$8, H4.B3,2, H4.P$1, H4.P$2, H4.P$3, H4.P$4, H4.P$5, H4.P$6, H4.P$7, H4.P$8, IC1.3 (GND), IC1.5 (GND), IC1.21 (AGND), IC2.3 (A2), IC2.4 (A1), IC2.5 (A0), IC2.9 (GND), IC3.1 (A0), IC3.2 (A1), IC3.3 (A2), IC3.4 (A3), IC3.5 (A4), IC3.14 (GND), IC3.24 (A5), IC3.25 (EXTCLK), IC4.7 (GND), IC5.2 (GND), IC5.8 (STBY), IC6.2 (GND), R34.1, R41.1, S9.A1 (1), S9.A2 (1), X1.4, X2.4, X3.6, X4.1, X4.2, XTAL1.2, XTAL1.4 (2), XTAL2.2, XTAL2.4 (2); also elsewhere on the board
I2C_SCL: IC1.28 (PC5(ADC5/SCL)), IC2.1 (SCL), IC3.26 (SCL), R36.1
I2C_SDA: IC1.27 (PC4(ADC4/SDA)), IC2.2 (SDA), IC3.27 (SDA), R35.2
IND_1: IC3.22 (PWM15); also elsewhere on the board
IND_2: IC3.21 (PWM14); also elsewhere on the board
IND_3: IC3.20 (PWM13); also elsewhere on the board
IND_4: IC3.19 (PWM12); also elsewhere on the board
IND_5: IC3.18 (PWM11); also elsewhere on the board
IND_6: IC3.17 (PWM10); also elsewhere on the board
IND_7: IC3.16 (PWM9); also elsewhere on the board
IND_8: IC3.15 (PWM8); also elsewhere on the board
INT_BTN: IC1.32 (PD2(INT0)), IC2.8 (INT)
INT_CAN: IC1.1 (PD3(INT1)), IC4.4 (INT)
LED: IC1.12 (PB0(ICP)), R38.2
unnamed: IC3.23 (#OE), R34.2
unnamed: D9.A, R37.1
unnamed: C4.1, IC1.7 (PB6(XTAL1/TOSC1)), XTAL1.1
unnamed: C5.1, IC1.8 (PB7(XTAL2/TOSC2)), XTAL1.3
unnamed: D10.A, R38.1
unnamed: C6.1, X4.6
unnamed: C14.2, IC6.6 (SW), L1.1
unnamed: IC6.3 (FB), R41.2, R42.1
unnamed: C14.1, IC6.1 (CB)
unnamed: IC5.6 (CANL), R43.1, X1.3, X2.3
unnamed: IC5.7 (CANH), JP1.1, X1.2, X2.2
unnamed: D11.C, IC4.1 (TXCAN), IC5.1 (TXD)
unnamed: D12.C, IC4.2 (RXCAN), IC5.4 (RXD)
unnamed: C9.2, IC4.5 (OSC2), XTAL2.1
unnamed: C10.2, IC4.6 (OSC1), XTAL2.3
unnamed: D11.A, R39.1
unnamed: D12.A, R40.1
unnamed: JP1.2, R43.2
OPTO_1: IC3.6 (PWM0); also elsewhere on the board
OPTO_2: IC3.7 (PWM1); also elsewhere on the board
OPTO_3: IC3.8 (PWM2); also elsewhere on the board
OPTO_4: IC3.9 (PWM3); also elsewhere on the board
OPTO_5: IC3.10 (PWM4); also elsewhere on the board
OPTO_6: IC3.11 (PWM5); also elsewhere on the board
OPTO_7: IC3.12 (PWM6); also elsewhere on the board
OPTO_8: IC3.13 (PWM7); also elsewhere on the board
RESET: C6.2, IC1.29 (PC6(/RESET)), IC2.6 (RESET), R33.1, S9.B1 (2), S9.B2 (2), X3.5
SEL_1: IC2.17 (GPIO7); also elsewhere on the board
SEL_2: IC2.16 (GPIO6); also elsewhere on the board
SEL_3: IC2.15 (GPIO5); also elsewhere on the board
SEL_4: IC2.14 (GPIO4); also elsewhere on the board
SEL_5: IC2.13 (GPIO3); also elsewhere on the board
SEL_6: IC2.12 (GPIO2); also elsewhere on the board
SEL_7: IC2.11 (GPIO1); also elsewhere on the board
SEL_8: IC2.10 (GPIO0); also elsewhere on the board
SPI_CLK: IC1.17 (PB5(SCK)), IC4.10 (SCK), X3.3
SPI_CS_CAN: IC1.14 (PB2(SS/OC1B)), IC4.13 (CS)
SPI_MISO: IC1.16 (PB4(MISO)), IC4.12 (SDO), X3.1
SPI_MOSI: IC1.15 (PB3(MOSI/OC2)), IC4.11 (SDI), X3.4
UART_RX: IC1.30 (PD0(RXD)), X4.4
UART_TX: IC1.31 (PD1(TXD)), X4.5
VCC: C1.1, C2.1, C3.1, C7.2, C8.1, C11.1, C12.2, C13.2, IC1.4 (VCC), IC1.6 (VCC), IC1.18 (AVCC), IC1.20 (AREF), IC2.18 (VCC), IC3.28 (VDD), IC4.14 (VCC), IC5.3 (VCC), IC5.5 (VIO), L1.2, R33.2, R35.1, R36.2, R37.2, R39.2, R40.2, R42.2, X3.2, X4.3
